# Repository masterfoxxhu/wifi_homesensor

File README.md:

# wifi_homesensor
Quick and dirty ESP8266 based thermo and humidity meter for ESPhome

Based around a Wemos D1 mini module, using SHT31 sensor, and a MCP16301 DCDC converter.\
Enclosure [PA62W](https://lomex.hu/hu/webshop/%23/search,47-02-16/stype,1)

A  render of the board.\
The sensor is located on the bottom of the board to minimise heat pickup from the rest of the board. There is a vent near the sensor on the enclosure.

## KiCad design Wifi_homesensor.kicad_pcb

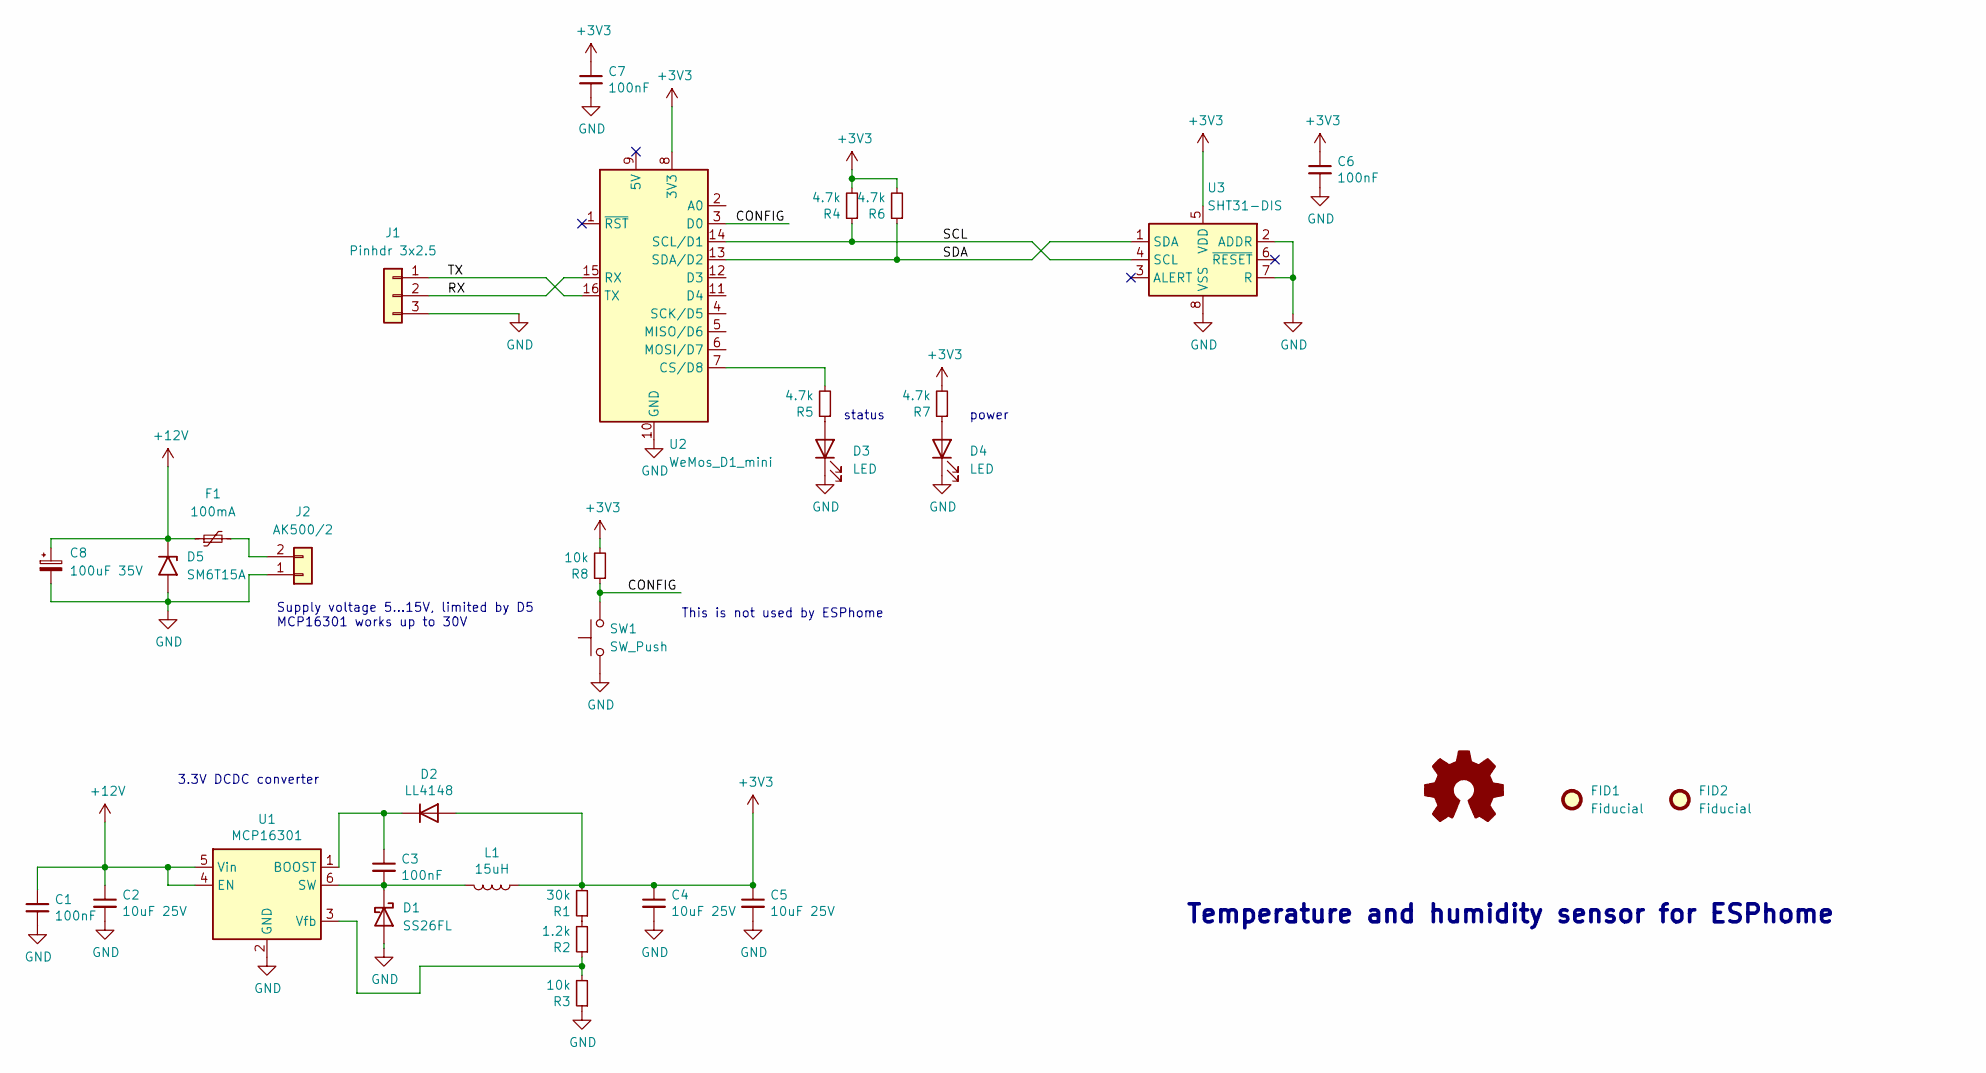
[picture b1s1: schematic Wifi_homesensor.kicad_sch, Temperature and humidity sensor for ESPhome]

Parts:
C1, C3, C6, C7: 100nF; C_0603_1608Metric
C2, C4, C5: 10uF 25V; C_1206_3216Metric
C8: 100uF 35V; C_Radial_D8.0mm_H11.5mm_P3.50mm
D1: SS26FL; D_SOD-123F
D2: LL4148; D_MiniMELF
D3, D4: LED; LED_0805_2012Metric
D5: SM6T15A; D_SMB
F1: 100mA; Fuse_1812_4532Metric
FID1, FID2: Fiducial; Fiducial_0.75mm_Mask2.25mm
J1: Pinhdr 3x2.5; PinHeader_1x03_P2.54mm_Vertical
J2: AK500/2; TerminalBlock_Phoenix_MKDS-1,5-2-5.08_1x02_P5.08mm_Horizont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
L1: 15uH; inductor_6_5x6_5
LOGO1: Logo_Open_Hardware_Small; OSHW-Logo2_14.6x12mm_SilkScreen
R1: 30k; R_0603_1608Metric
R2: 1.2k; R_0603_1608Metric
R3, R8: 10k; R_0603_1608Metric
R4, R5, R6, R7: 4.7k; R_0603_1608Metric
SW1: SW_Push; SW_Tactile_SPST_Angled_PTS645Vx83-2LFS
U1: MCP16301; SOT-23-6
U2: WeMos_D1_mini; WEMOS_D1_mini_light
U3: SHT31-DIS; Sensirion_DFN-8-1EP_2.5x2.5mm_P0.5mm_EP1.1x1.7mm

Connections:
+3V3: C4.1, C5.1, C6.1, C7.1, D2.2 (A), L1.1, R1.2, R4.2, R6.2, R7.2, R8.2, U2.8 (3V3), U3.5 (VDD)
+12V: C1.1, C2.1, C8.1, D5.1 (A1), F1.1, U1.4 (EN), U1.5 (Vin)
/CONFIG: R8.1, SW1.2, U2.3 (D0)
/RX: J1.2, U2.15 (RX)
/SCL: R4.1, U2.14 (SCL/D1), U3.4 (SCL)
/SDA: R6.1, U2.13 (SDA/D2), U3.1 (SDA)
/TX: J1.1, U2.16 (TX)
GND: C1.2, C2.2, C4.2, C5.2, C6.2, C7.2, C8.2, D1.2 (A), D3.1 (K), D4.1 (K), D5.2 (A2), J1.3, J2.1, R3.1, SW1.1, U1.2 (GND), U2.10 (GND), U3.2 (ADDR), U3.7 (R), U3.8 (VSS), U3.9 (VSS)
unnamed: C3.1, D2.1 (K), U1.1 (BOOST)
unnamed: C3.2, D1.1 (K), L1.2, U1.6 (SW)
unnamed: D3.2 (A), R5.1
unnamed: D4.2 (A), R7.1
unnamed: F1.2, J2.2
unnamed: R1.1, R2.2
unnamed: R2.1, R3.2, U1.3 (Vfb)
unnamed: R5.2, U2.7 (CS/D8)

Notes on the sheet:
Temperature and humidity sensor for ESPhome
status
This is not used by ESPhome
3.3V DCDC converter
Supply voltage 5...15V, limited by D5 MCP16301 works up to 30V
power

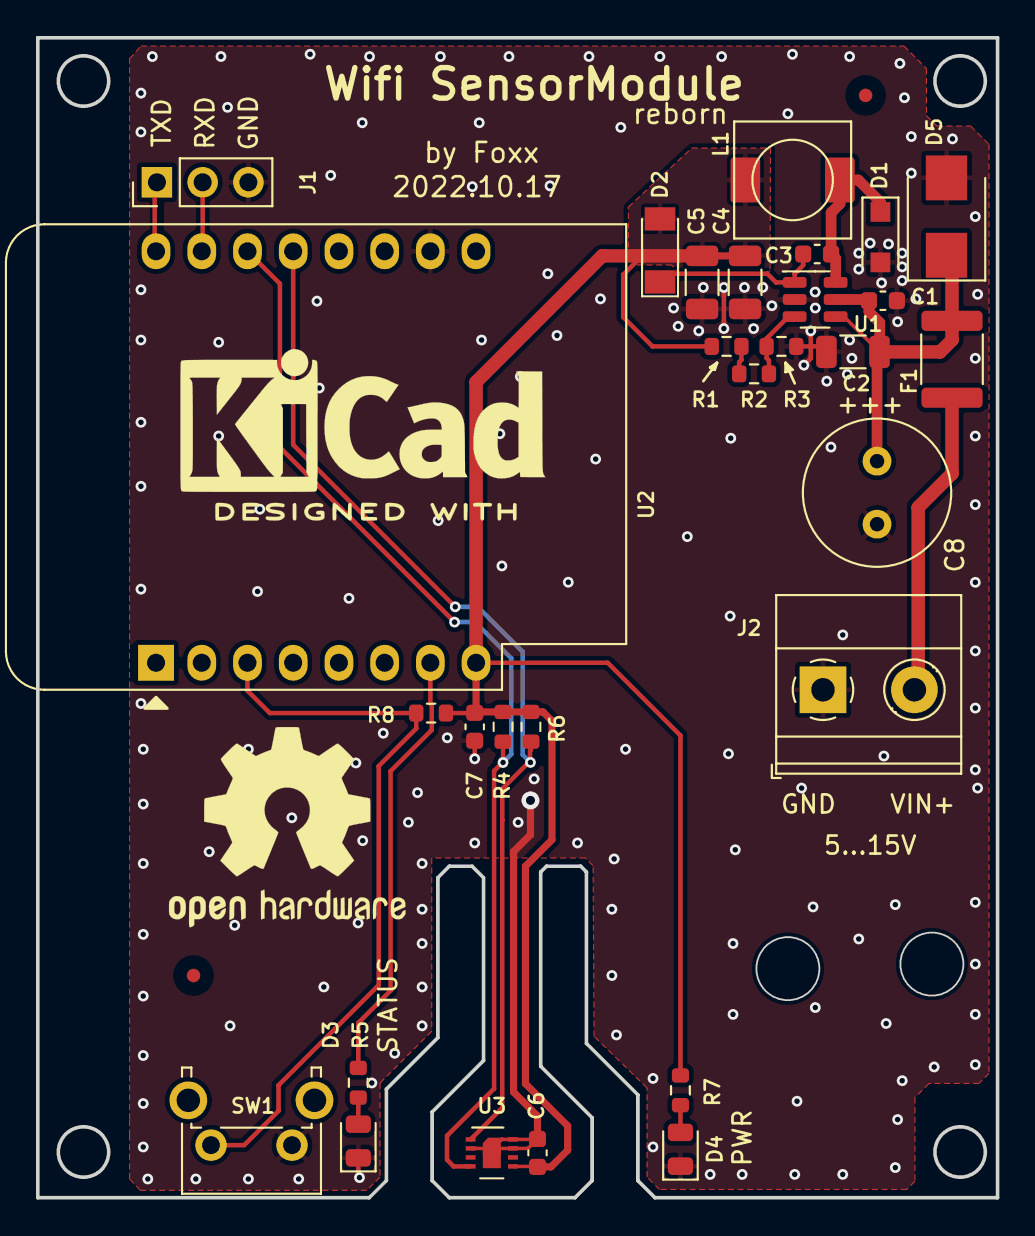
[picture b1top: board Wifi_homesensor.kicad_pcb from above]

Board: 2 copper layers, 53.3 x 64.4 mm, 33 parts (0 on the bottom side), 16 nets.

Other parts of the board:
LOGO2: KiCad-Logo2_8mm_SilkScreen

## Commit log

2022-10-08 schematic almost finished
2022-10-08 readme edite
2022-10-15 schematic finished, pcb editing started
2022-10-17 pcb finished
